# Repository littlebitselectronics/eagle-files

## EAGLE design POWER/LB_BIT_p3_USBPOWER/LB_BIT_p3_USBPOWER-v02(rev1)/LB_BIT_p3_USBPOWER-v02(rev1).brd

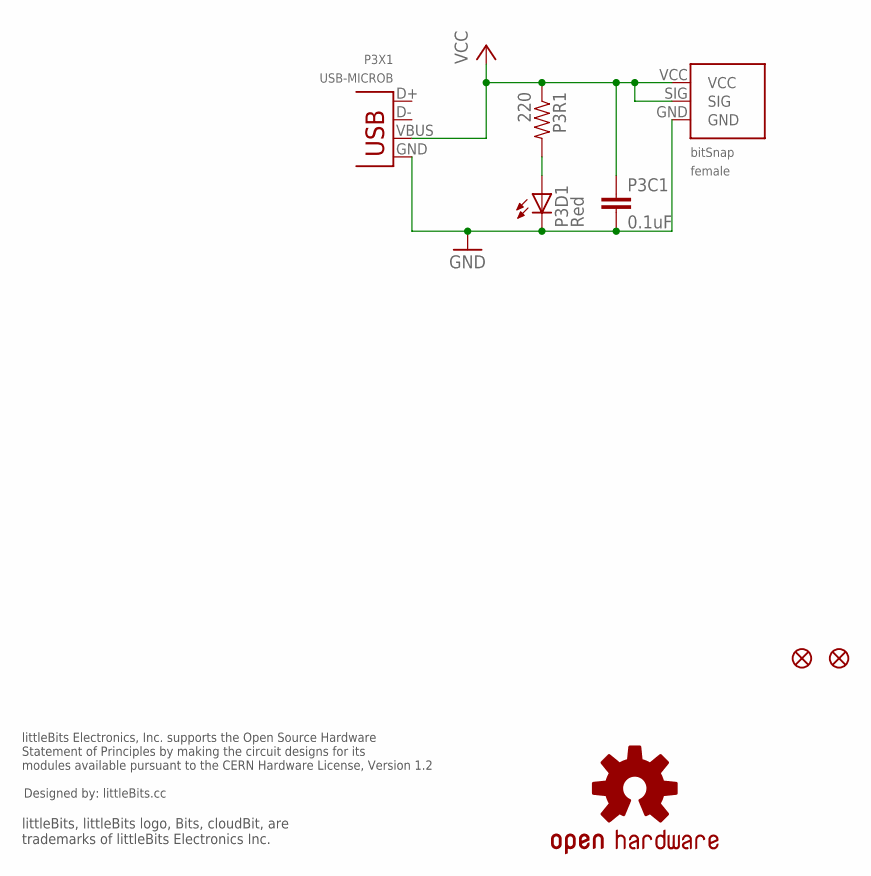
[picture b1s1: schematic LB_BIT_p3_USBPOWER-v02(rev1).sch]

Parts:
P3BSF: BITSNAP_FEMALE
P3C1: 0.1uF; 0603-CAP
P3D1: Red; LED-1206
P3FD1, P3FD2: FIDUCIAL1X2; FIDUCIAL-1X2
P3R1: 220; 0603-RES
P3X1: USB-MICROB; USB-MICROB-ZX62-B-5PA(11)
U$2: OSHWCREDIT
U$3: OSHW-LOGOL; OSHW-LOGO-L

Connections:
GND: P3BSF.GND, P3C1.2, P3D1.C, P3X1.GND
unnamed: P3D1.A, P3R1.2
VCC: P3BSF.SIG, P3BSF.VCC, P3C1.1, P3R1.1, P3X1.VBUS

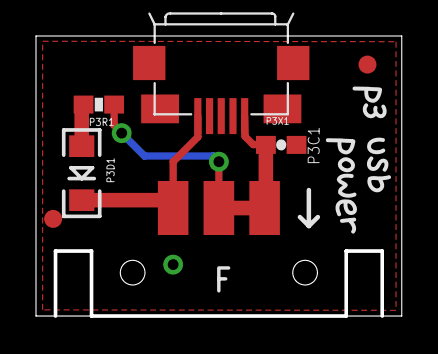
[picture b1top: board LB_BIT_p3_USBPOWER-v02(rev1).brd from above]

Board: 2 copper layers, 20.3 x 15.6 mm, 20 parts (0 on the bottom side), 3 nets.

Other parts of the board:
U$1, U$10: P
U$4: OSHW_FILLX150_NOTEXT
U$6: 3
U$7: U
U$8: S
U$9: B
U$11: O
U$12: W
U$13: E
U$14: R

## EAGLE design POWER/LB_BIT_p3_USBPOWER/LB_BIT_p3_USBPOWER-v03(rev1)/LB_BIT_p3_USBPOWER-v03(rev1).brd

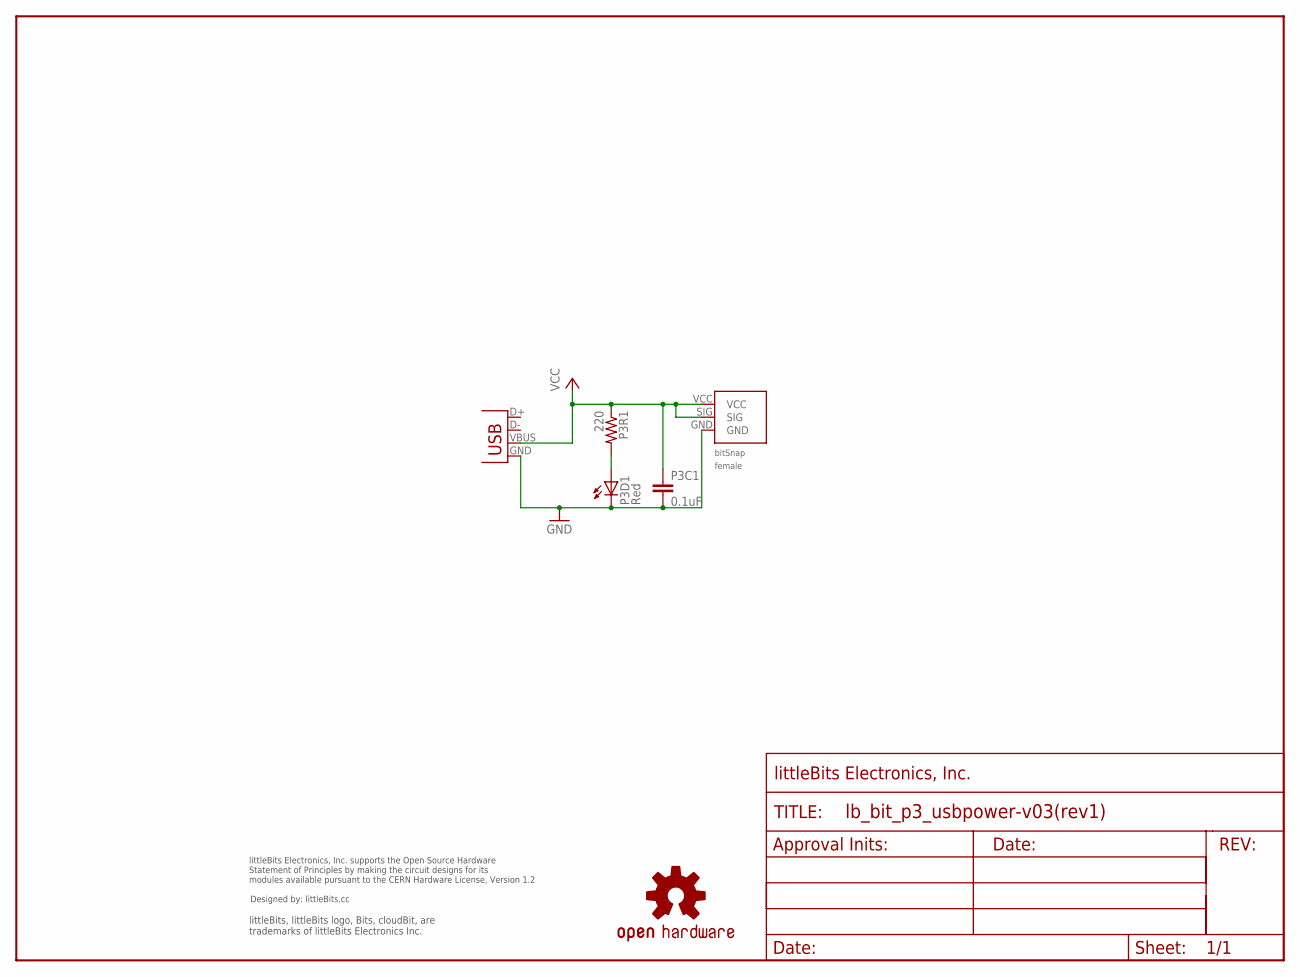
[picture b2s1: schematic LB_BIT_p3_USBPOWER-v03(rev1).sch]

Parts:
P3BSF1: BITSNAP_V03_FEMALE
P3C1: 0.1uF; 0603-CAP
P3D1: Red; LED-1206
P3R1: 220; 0603-RES
P3X1: USB-MICROB-AUK_TH; USB-MICROB-AUK
U$1: OSHWCREDIT
U$2: FRAME-LETTER-OHWOHW; FABDWG01-OHW
U$3: OSHW-LOGOL; OSHW-LOGO-L

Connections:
GND: P3BSF1.GND, P3C1.2, P3D1.C, P3X1.GND
unnamed: P3D1.A, P3R1.2
VCC: P3BSF1.SIG, P3BSF1.VCC, P3C1.1, P3R1.1, P3X1.VBUS

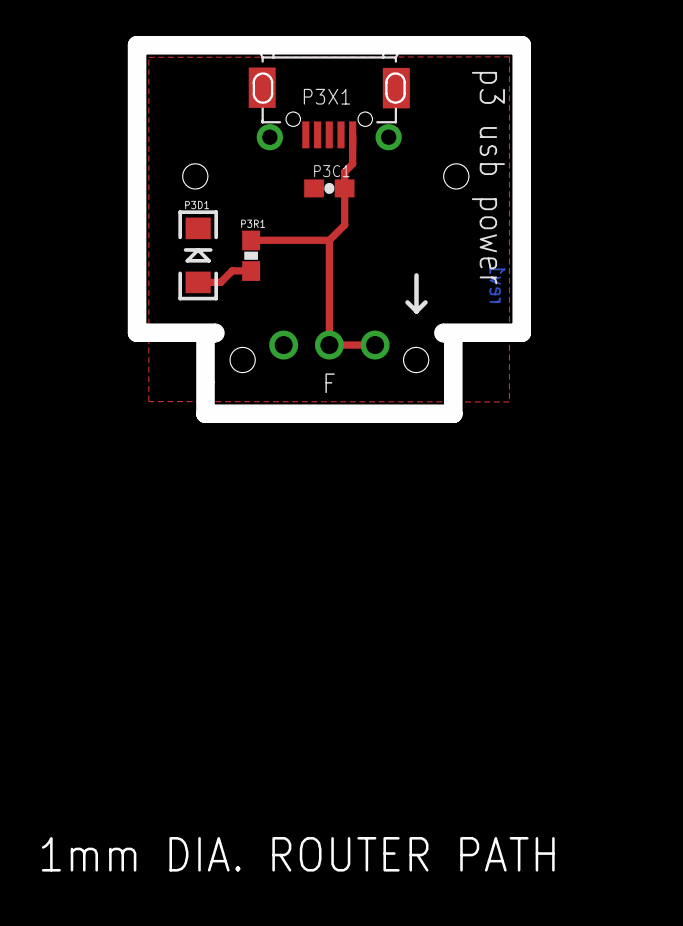
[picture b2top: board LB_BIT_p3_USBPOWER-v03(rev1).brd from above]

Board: 2 copper layers, 21.4 x 20.5 mm, 10 parts (0 on the bottom side), 3 nets.

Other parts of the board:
U$4: OSHW_FILLX150_NOTEXT
U$15: LB_PWR_LEGS

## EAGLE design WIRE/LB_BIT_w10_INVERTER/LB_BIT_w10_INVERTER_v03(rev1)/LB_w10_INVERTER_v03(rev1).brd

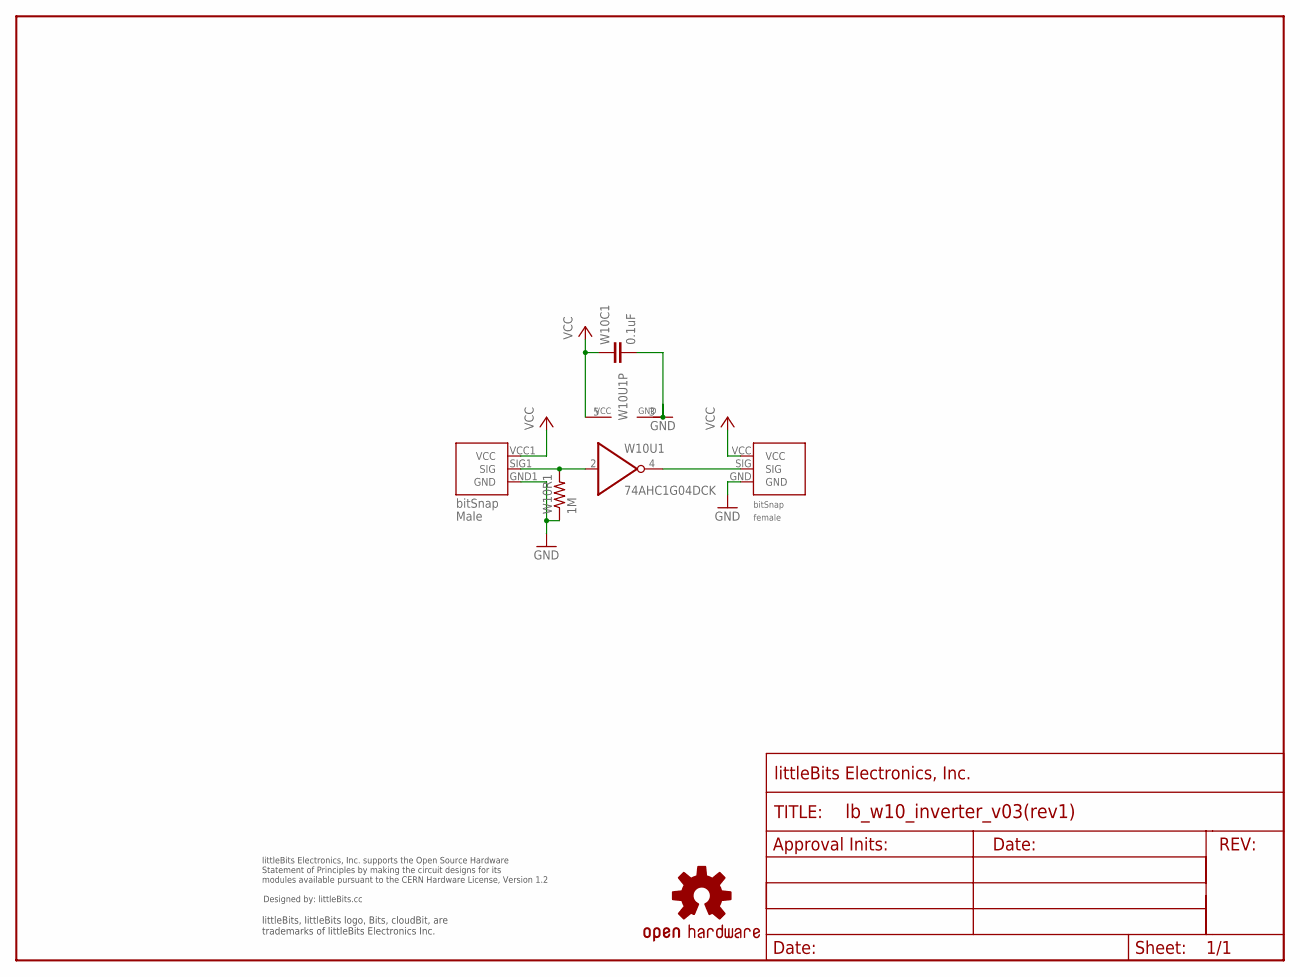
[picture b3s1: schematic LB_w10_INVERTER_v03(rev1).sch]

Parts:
U$1: FRAME-LETTER-OHWOHW; FABDWG01-OHW
U$3: OSHWCREDIT
U$4: OSHW-LOGOL; OSHW-LOGO-L
W10BSF1: BITSNAP_V03_FEMALE
W10BSM1: BITSNAP_V03_MALE
W10C1: 0.1uF; 0603-CAP
W10R1: 1M; 0603-RES
W10U1: 74AHC1G04DCK; SC70-5

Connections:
GND: W10BSF1.GND, W10BSM1.GND1 (GND), W10C1.2, W10R1.1, W10U1.3 (GND)
unnamed: W10BSM1.SIG1 (SIG), W10R1.2, W10U1.2 (I)
unnamed: W10BSF1.SIG, W10U1.4 (O)
VCC: W10BSF1.VCC, W10BSM1.VCC1 (VCC), W10C1.1, W10U1.5 (VCC)

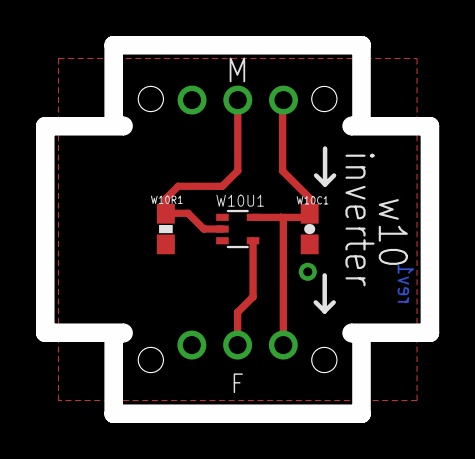
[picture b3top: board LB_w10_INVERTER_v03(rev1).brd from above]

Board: 2 copper layers, 21.4 x 20.5 mm, 9 parts (0 on the bottom side), 4 nets.

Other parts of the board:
U$2: OSHW_FILLX150_NOTEXT

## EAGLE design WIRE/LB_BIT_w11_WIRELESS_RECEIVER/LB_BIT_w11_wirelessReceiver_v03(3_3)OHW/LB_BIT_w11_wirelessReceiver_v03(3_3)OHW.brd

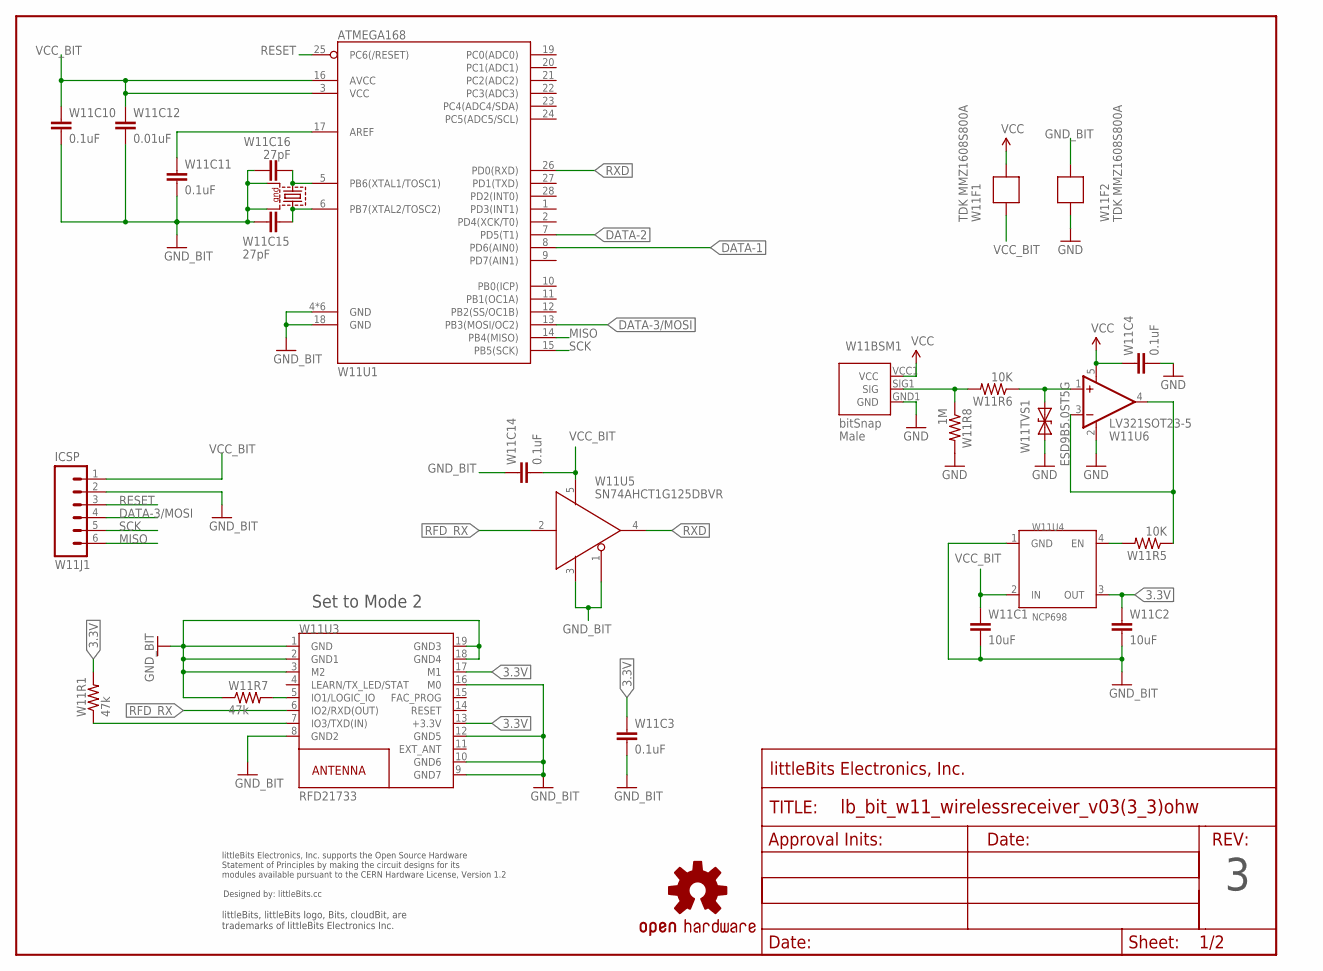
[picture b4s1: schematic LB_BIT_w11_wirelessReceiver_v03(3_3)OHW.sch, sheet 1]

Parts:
FRAME1: FRAME-LETTER-OHWOHW; FABDWG01-OHW
U$3: OSHW-LOGOL; OSHW-LOGO-L
U$7: OSHWCREDIT
W11BSM1: BITSNAP_V03_MALE
W11C1, W11C2: 10uF; CAP-0603
W11C3, W11C4, W11C10, W11C11, W11C14: 0.1uF; CAP-0603
W11C12: 0.01uF; CAP-0603
W11C15, W11C16: 27pF; CAP-0603
W11F1, W11F2: TDK MMZ1608S800A; R0603
W11J1: ICSP; SIP6-SM-0.1IN-NOS.S.
W11R1, W11R7: 47k; RES-0603
W11R5, W11R6: 10K; RES-0603
W11R8: 1M; RES-0603
W11TVS1: ESD9B5.0ST5G; SOD-923
W11U1: ATMEGA168; VQFN28
W11U3: RFD21733
W11U4: NCP698; NCP698_SC82-AB
W11U5: SN74AHCT1G125DBVR; SOT23-5
W11U6: LV321SOT23-5; SOT23-5
W11X1: 7B-8.000MAAJ-T; CRYSTAL-SMD-7B-SERIES-5X3.2MM

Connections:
3.3V: W11C2.1, W11C3.1, W11R1.2, W11U3.13 (+3.3V), W11U3.17 (M1), W11U4.3 (OUT)
DATA-1: W11U1.8 (PD6(AIN0)); also elsewhere on the board
DATA-2: W11U1.7 (PD5(T1)); also elsewhere on the board
DATA-3/MOSI: W11J1.4, W11U1.13 (PB3(MOSI/OC2)); also elsewhere on the board
ENABLE: W11R5.2, W11U4.4 (EN)
GND: W11BSM1.GND1 (GND), W11C4.2, W11F2.2, W11R8.2, W11TVS1.1 (A), W11U6.2 (V-); also elsewhere on the board
GND_BIT: W11C1.2, W11C2.2, W11C3.2, W11C10.2, W11C11.2, W11C12.2, W11C14.1, W11C15.2, W11C16.1, W11F2.1, W11J1.2, W11R7.1, W11U1.4 (GND), W11U1.18 (GND), W11U1.TH (GND), W11U1.TH@1 (GND), W11U1.TH@2 (GND), W11U1.TH@3 (GND), W11U1.TH@4 (GND), W11U3.1 (GND), W11U3.2 (GND1), W11U3.3 (M2), W11U3.8 (GND2), W11U3.9 (GND7), W11U3.10 (GND6), W11U3.12 (GND5), W11U3.16 (M0), W11U3.18 (GND4), W11U3.19 (GND3), W11U4.1 (GND), W11U5.1, W11U5.3, W11X1.P$2 (2), W11X1.P$4 (4)
MISO: W11J1.6, W11U1.14 (PB4(MISO))
unnamed: W11R6.1, W11TVS1.2 (C), W11U6.1 (+IN)
unnamed: W11C11.1, W11U1.17 (AREF)
unnamed: W11R7.2, W11U3.5 (IO1/LOGIC_IO)
unnamed: W11BSM1.SIG1 (SIG), W11R6.2, W11R8.1
unnamed: W11C16.2, W11U1.5 (PB6(XTAL1/TOSC1)), W11X1.P$1 (1)
unnamed: W11C15.1, W11U1.6 (PB7(XTAL2/TOSC2)), W11X1.P$3 (3)
unnamed: W11R5.1, W11U6.3 (-IN), W11U6.4 (OUT)
RESET: W11J1.3, W11U1.25 (PC6(/RESET))
RFD_RX: W11U3.6 (IO2/RXD(OUT)), W11U5.2
RFD_TX: W11R1.1, W11U3.7 (IO3/TXD(IN))
RXD: W11U1.26 (PD0(RXD)), W11U5.4
SCK: W11J1.5, W11U1.15 (PB5(SCK))
VCC: W11BSM1.VCC1 (VCC), W11C4.1, W11F1.1, W11U6.5 (V+); also elsewhere on the board
VCC_BIT: W11C1.1, W11C10.1, W11C12.1, W11C14.2, W11F1.2, W11J1.1, W11U1.3 (VCC), W11U1.16 (AVCC), W11U4.2 (IN), W11U5.5

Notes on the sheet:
Set to Mode 2

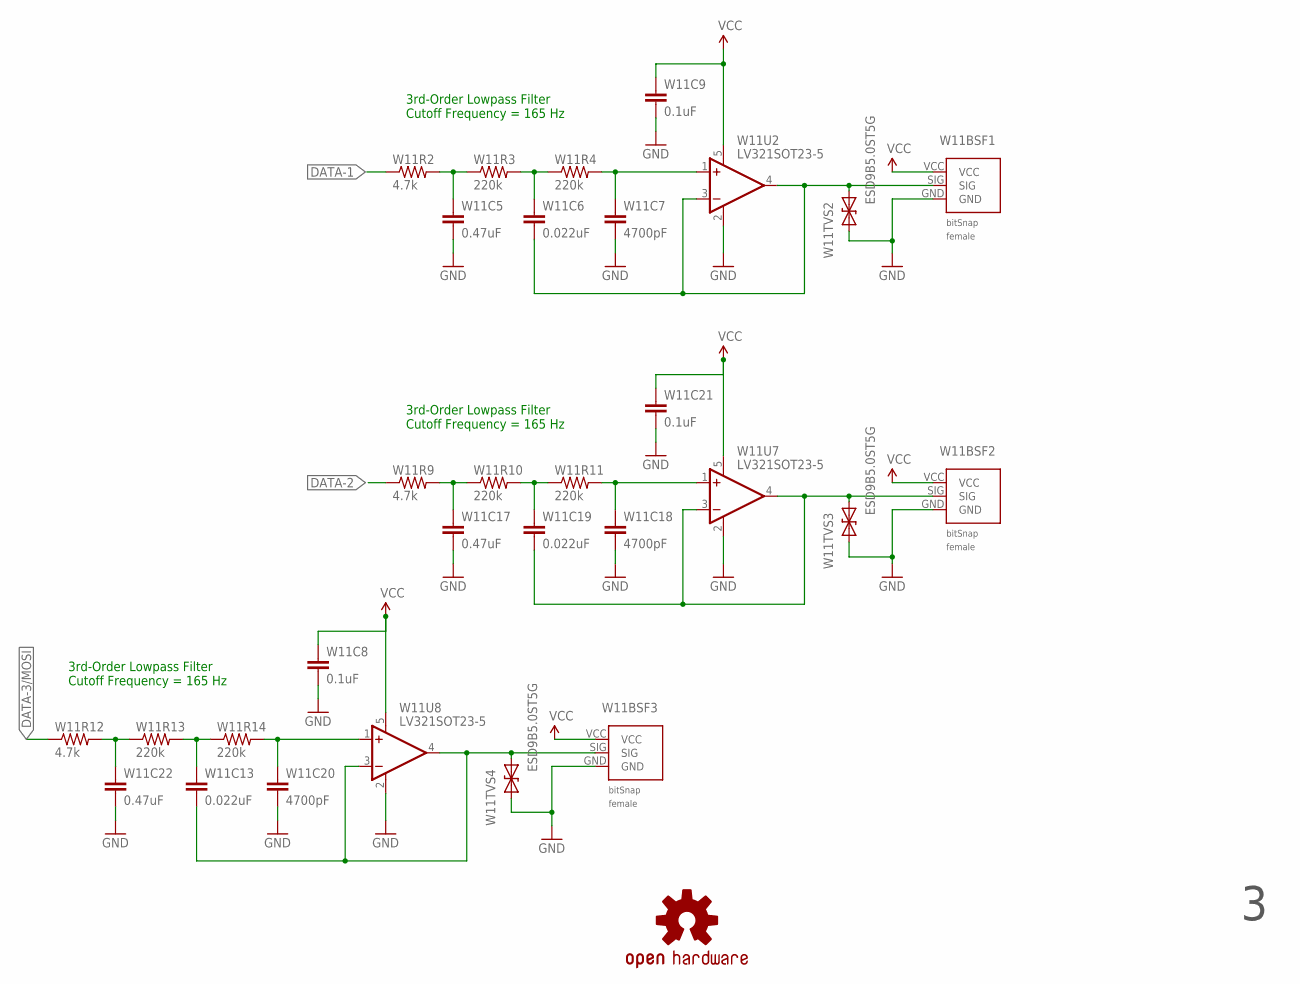
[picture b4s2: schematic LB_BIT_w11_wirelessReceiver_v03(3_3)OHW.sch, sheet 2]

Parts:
U$9: OSHW-LOGOL; OSHW-LOGO-L
W11BSF1, W11BSF2, W11BSF3: BITSNAP_V03_FEMALE
W11C5, W11C17, W11C22: 0.47uF; CAP-0603
W11C6, W11C13, W11C19: 0.022uF; CAP-0603
W11C7, W11C18, W11C20: 4700pF; CAP-0603
W11C8, W11C9, W11C21: 0.1uF; CAP-0603
W11R2, W11R9, W11R12: 4.7k; RES-0603
W11R3, W11R4, W11R10, W11R11, W11R13, W11R14: 220k; RES-0603
W11TVS2, W11TVS3, W11TVS4: ESD9B5.0ST5G; SOD-923
W11U2, W11U7, W11U8: LV321SOT23-5; SOT23-5

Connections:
DATA-1: W11R2.1; also elsewhere on the board
DATA-2: W11R9.1; also elsewhere on the board
DATA-3/MOSI: W11R12.1; also elsewhere on the board
GND: W11BSF1.GND, W11BSF2.GND, W11BSF3.GND, W11C5.2, W11C7.2, W11C8.2, W11C9.2, W11C17.2, W11C18.2, W11C20.2, W11C21.2, W11C22.2, W11TVS2.1 (A), W11TVS3.1 (A), W11TVS4.1 (A), W11U2.2 (V-), W11U7.2 (V-), W11U8.2 (V-); also elsewhere on the board
unnamed: W11C6.1, W11R3.2, W11R4.1
unnamed: W11C5.1, W11R2.2, W11R3.1
unnamed: W11C7.1, W11R4.2, W11U2.1 (+IN)
unnamed: W11C17.1, W11R9.2, W11R10.1
unnamed: W11C18.1, W11R11.2, W11U7.1 (+IN)
unnamed: W11C19.1, W11R10.2, W11R11.1
unnamed: W11C22.1, W11R12.2, W11R13.1
unnamed: W11C20.1, W11R14.2, W11U8.1 (+IN)
unnamed: W11C13.1, W11R13.2, W11R14.1
OUT-1: W11BSF1.SIG, W11C6.2, W11TVS2.2 (C), W11U2.3 (-IN), W11U2.4 (OUT)
OUT-2: W11BSF2.SIG, W11C19.2, W11TVS3.2 (C), W11U7.3 (-IN), W11U7.4 (OUT)
OUT-3: W11BSF3.SIG, W11C13.2, W11TVS4.2 (C), W11U8.3 (-IN), W11U8.4 (OUT)
VCC: W11BSF1.VCC, W11BSF2.VCC, W11BSF3.VCC, W11C8.1, W11C9.1, W11C21.1, W11U2.5 (V+), W11U7.5 (V+), W11U8.5 (V+); also elsewhere on the board

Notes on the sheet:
3rd-Order Lowpass Filter Cutoff Frequency = 165 Hz

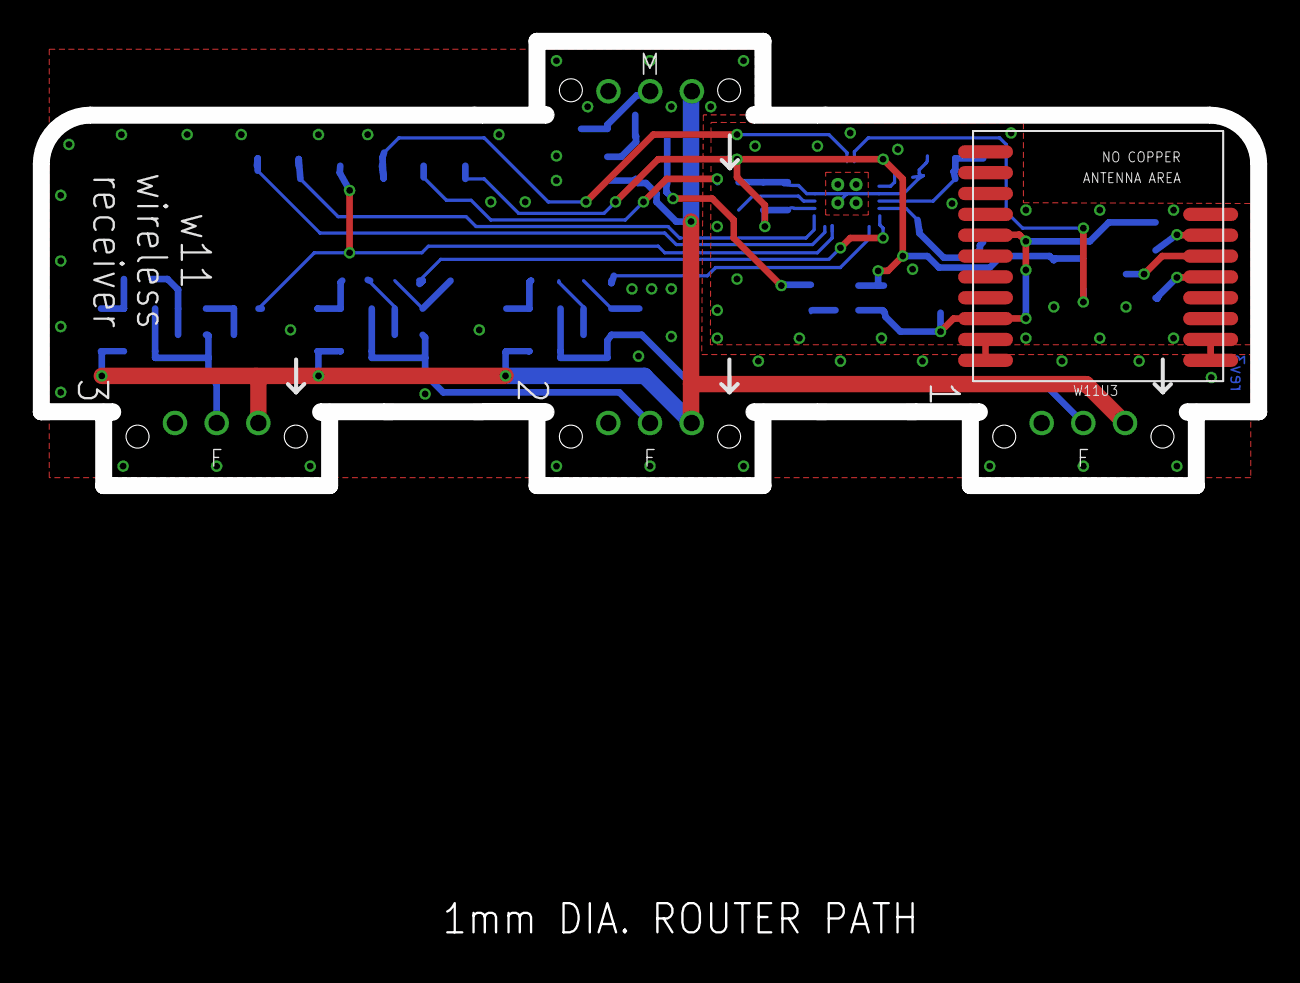
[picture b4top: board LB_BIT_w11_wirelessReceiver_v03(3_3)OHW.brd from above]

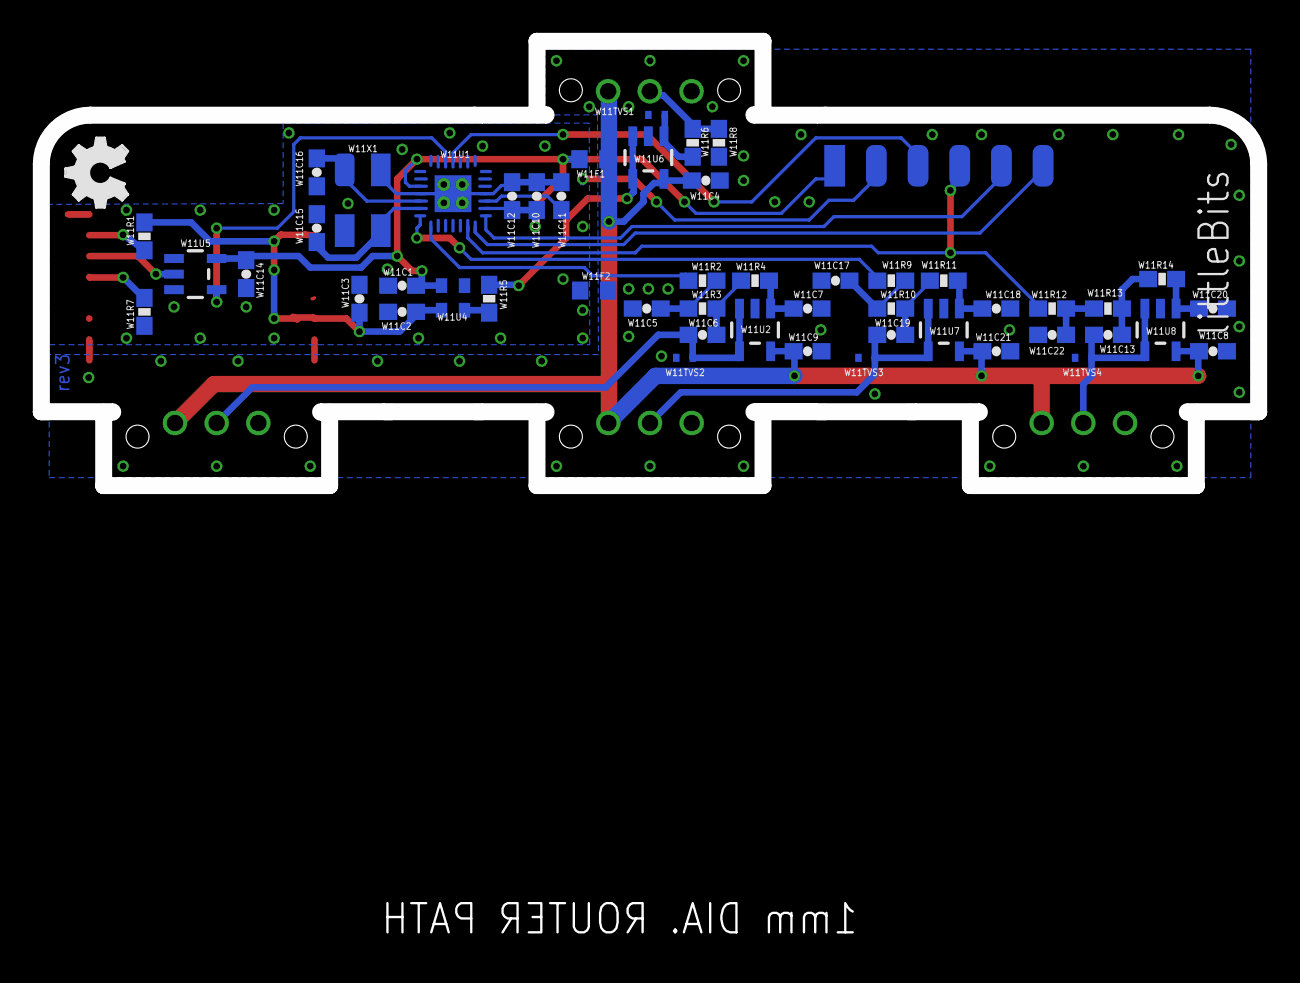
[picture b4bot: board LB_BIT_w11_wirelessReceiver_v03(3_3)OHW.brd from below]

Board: 2 copper layers, 74.2 x 27.1 mm, 61 parts (51 on the bottom side), 34 nets.

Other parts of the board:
U$21: OSHW_FILLX150_NOTEXT

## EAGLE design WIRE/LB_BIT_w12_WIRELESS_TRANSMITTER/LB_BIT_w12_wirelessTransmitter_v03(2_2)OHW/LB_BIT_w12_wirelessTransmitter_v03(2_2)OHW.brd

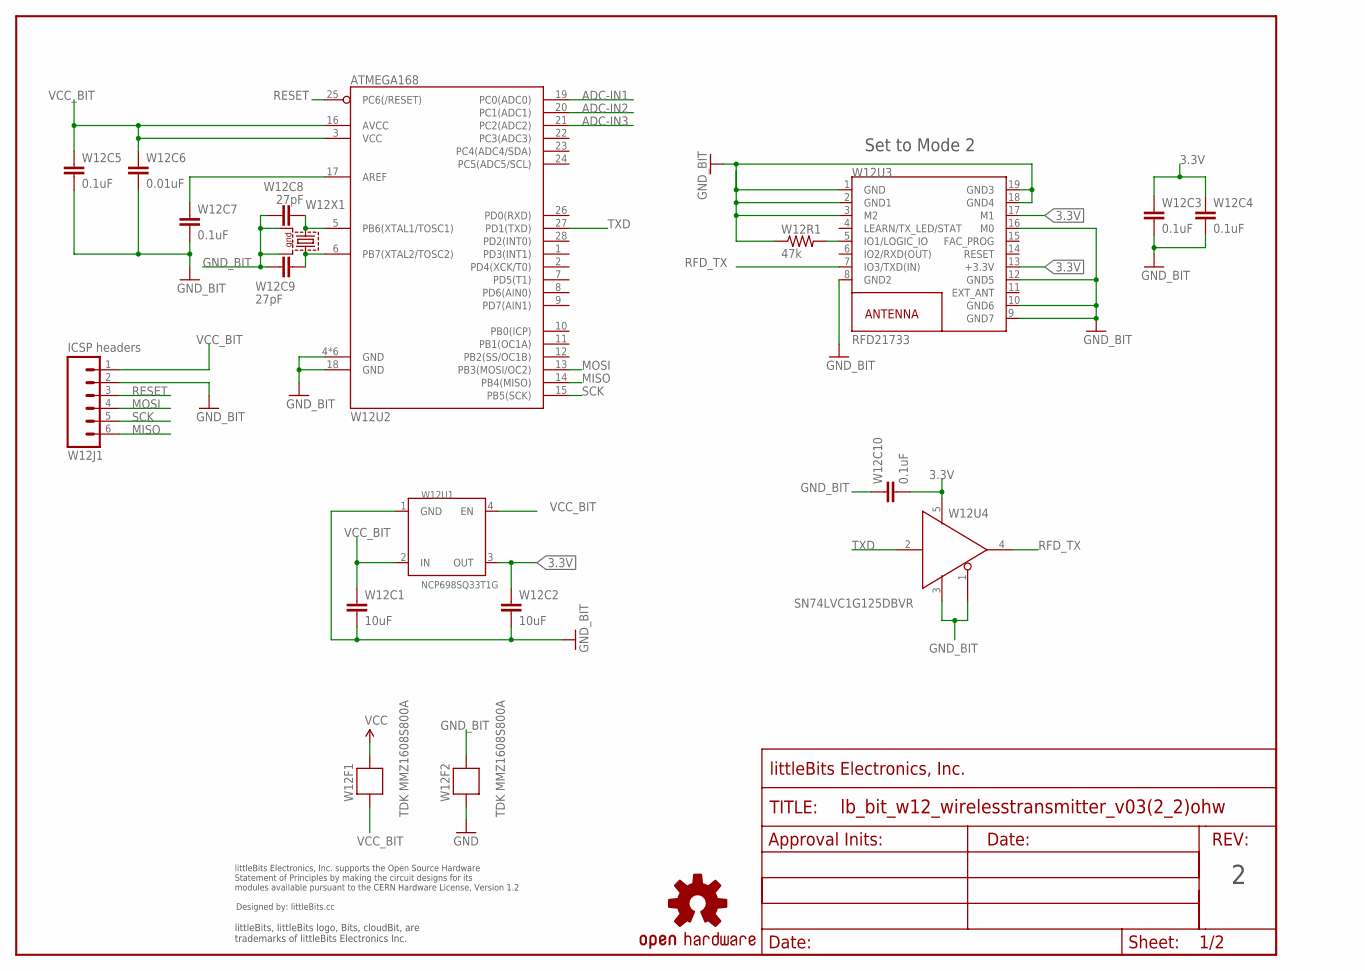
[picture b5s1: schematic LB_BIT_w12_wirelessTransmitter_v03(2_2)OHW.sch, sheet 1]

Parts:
FRAME1: FRAME-LETTER-OHWOHW; FABDWG01-OHW
U$15: OSHWCREDIT
U$31: OSHW-LOGOL; OSHW-LOGO-L
W12C1, W12C2: 10uF; CAP-0603
W12C3, W12C4, W12C5, W12C7, W12C10: 0.1uF; 0603-CAP
W12C6: 0.01uF; 0603-CAP
W12C8, W12C9: 27pF; CAP-0603
W12F1, W12F2: TDK MMZ1608S800A; R0603
W12J1: ICSP headers; SIP6-SM-0.1IN-NOS.S.
W12R1: 47k; 0603-RES
W12U1: NCP698SQ33T1G; NCP698_SC82-AB
W12U2: ATMEGA168; VQFN28
W12U3: RFD21733
W12U4: SN74LVC1G125DBVR; SOT23-5
W12X1: 8MHz; CRYSTAL-SMD-7B-SERIES-5X3.2MM

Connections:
3.3V: W12C2.1, W12C3.1, W12C4.1, W12C10.2, W12U1.3 (OUT), W12U3.13 (+3.3V), W12U3.17 (M1), W12U4.5
ADC-IN1: W12U2.19 (PC0(ADC0)); also elsewhere on the board
ADC-IN2: W12U2.20 (PC1(ADC1)); also elsewhere on the board
ADC-IN3: W12U2.21 (PC2(ADC2)); also elsewhere on the board
GND: W12F2.2; also elsewhere on the board
GND_BIT: W12C1.2, W12C2.2, W12C3.2, W12C4.2, W12C5.2, W12C6.2, W12C7.2, W12C8.1, W12C9.2, W12C10.1, W12F2.1, W12J1.2, W12R1.1, W12U1.1 (GND), W12U2.4 (GND), W12U2.18 (GND), W12U2.TH (GND), W12U2.TH@1 (GND), W12U2.TH@2 (GND), W12U2.TH@3 (GND), W12U2.TH@4 (GND), W12U3.1 (GND), W12U3.2 (GND1), W12U3.3 (M2), W12U3.8 (GND2), W12U3.9 (GND7), W12U3.10 (GND6), W12U3.12 (GND5), W12U3.16 (M0), W12U3.18 (GND4), W12U3.19 (GND3), W12U4.1, W12U4.3, W12X1.P$2 (2), W12X1.P$4 (4)
MISO: W12J1.6, W12U2.14 (PB4(MISO))
MOSI: W12J1.4, W12U2.13 (PB3(MOSI/OC2))
unnamed: W12C7.1, W12U2.17 (AREF)
unnamed: W12R1.2, W12U3.5 (IO1/LOGIC_IO)
unnamed: W12C8.2, W12U2.5 (PB6(XTAL1/TOSC1)), W12X1.P$1 (1)
unnamed: W12C9.1, W12U2.6 (PB7(XTAL2/TOSC2)), W12X1.P$3 (3)
RESET: W12J1.3, W12U2.25 (PC6(/RESET))
RFD_TX: W12U3.7 (IO3/TXD(IN)), W12U4.4
SCK: W12J1.5, W12U2.15 (PB5(SCK))
TXD: W12U2.27 (PD1(TXD)), W12U4.2
VCC: W12F1.1; also elsewhere on the board
VCC_BIT: W12C1.1, W12C5.1, W12C6.1, W12F1.2, W12J1.1, W12U1.2 (IN), W12U1.4 (EN), W12U2.3 (VCC), W12U2.16 (AVCC)

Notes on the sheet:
Set to Mode 2
W12X1

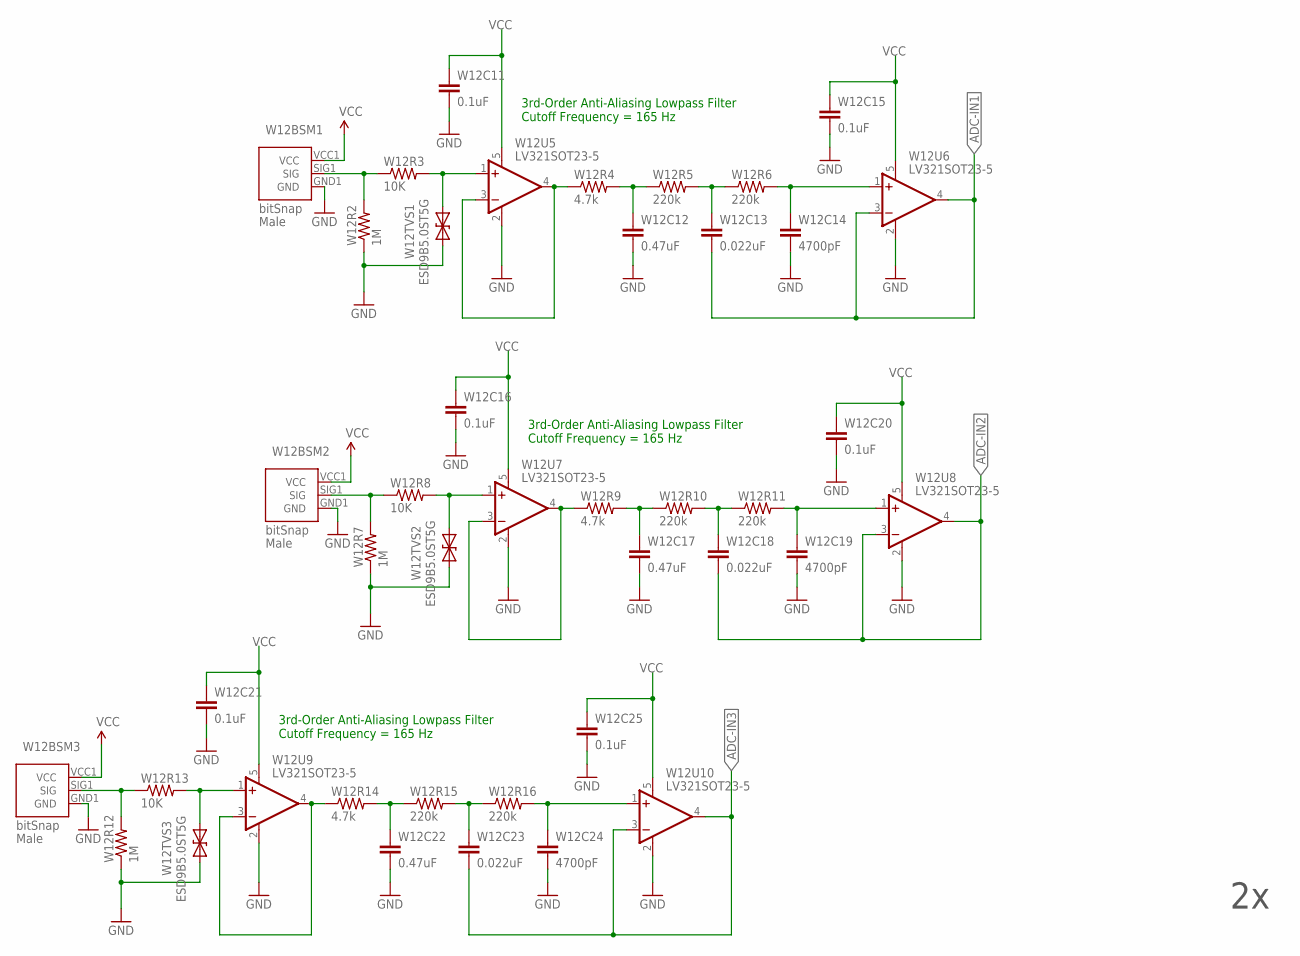
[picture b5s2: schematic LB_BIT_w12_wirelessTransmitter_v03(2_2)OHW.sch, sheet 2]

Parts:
W12BSM1, W12BSM2, W12BSM3: BITSNAP_V03_MALE
W12C11, W12C15, W12C16, W12C20, W12C21, W12C25: 0.1uF; 0603-CAP
W12C12, W12C17, W12C22: 0.47uF; CAP-0603
W12C13, W12C18, W12C23: 0.022uF; CAP-0603
W12C14, W12C19, W12C24: 4700pF; CAP-0603
W12R2, W12R7, W12R12: 1M; 0603-RES
W12R3, W12R8, W12R13: 10K; 0603-RES
W12R4, W12R9, W12R14: 4.7k; RES-0603
W12R5, W12R6, W12R10, W12R11, W12R15, W12R16: 220k; RES-0603
W12TVS1, W12TVS2, W12TVS3: ESD9B5.0ST5G; SOD-923
W12U5, W12U6, W12U7, W12U8, W12U9, W12U10: LV321SOT23-5; SOT23-5

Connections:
ADC-IN1: W12C13.2, W12U6.3 (-IN), W12U6.4 (OUT); also elsewhere on the board
ADC-IN2: W12C18.2, W12U8.3 (-IN), W12U8.4 (OUT); also elsewhere on the board
ADC-IN3: W12C23.2, W12U10.3 (-IN), W12U10.4 (OUT); also elsewhere on the board
GND: W12BSM1.GND1 (GND), W12BSM2.GND1 (GND), W12BSM3.GND1 (GND), W12C11.2, W12C12.2, W12C14.2, W12C15.2, W12C16.2, W12C17.2, W12C19.2, W12C20.2, W12C21.2, W12C22.2, W12C24.2, W12C25.2, W12R2.1, W12R7.1, W12R12.1, W12TVS1.1 (A), W12TVS2.1 (A), W12TVS3.1 (A), W12U5.2 (V-), W12U6.2 (V-), W12U7.2 (V-), W12U8.2 (V-), W12U9.2 (V-), W12U10.2 (V-); also elsewhere on the board
unnamed: W12R3.2, W12TVS1.2 (C), W12U5.1 (+IN)
unnamed: W12C12.1, W12R4.2, W12R5.1
unnamed: W12C14.1, W12R6.2, W12U6.1 (+IN)
unnamed: W12R4.1, W12U5.3 (-IN), W12U5.4 (OUT)
unnamed: W12C13.1, W12R5.2, W12R6.1
unnamed: W12R8.2, W12TVS2.2 (C), W12U7.1 (+IN)
unnamed: W12C17.1, W12R9.2, W12R10.1
unnamed: W12C19.1, W12R11.2, W12U8.1 (+IN)
unnamed: W12R9.1, W12U7.3 (-IN), W12U7.4 (OUT)
unnamed: W12C18.1, W12R10.2, W12R11.1
unnamed: W12R13.2, W12TVS3.2 (C), W12U9.1 (+IN)
unnamed: W12C22.1, W12R14.2, W12R15.1
unnamed: W12C24.1, W12R16.2, W12U10.1 (+IN)
unnamed: W12R14.1, W12U9.3 (-IN), W12U9.4 (OUT)
unnamed: W12C23.1, W12R15.2, W12R16.1
SIG3: W12BSM1.SIG1 (SIG), W12R2.2, W12R3.1
SIG4: W12BSM2.SIG1 (SIG), W12R7.2, W12R8.1
SIG5: W12BSM3.SIG1 (SIG), W12R12.2, W12R13.1
VCC: W12BSM1.VCC1 (VCC), W12BSM2.VCC1 (VCC), W12BSM3.VCC1 (VCC), W12C11.1, W12C15.1, W12C16.1, W12C20.1, W12C21.1, W12C25.1, W12U5.5 (V+), W12U6.5 (V+), W12U7.5 (V+), W12U8.5 (V+), W12U9.5 (V+), W12U10.5 (V+); also elsewhere on the board

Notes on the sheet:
3rd-Order Anti-Aliasing Lowpass Filter Cutoff Frequency = 165 Hz

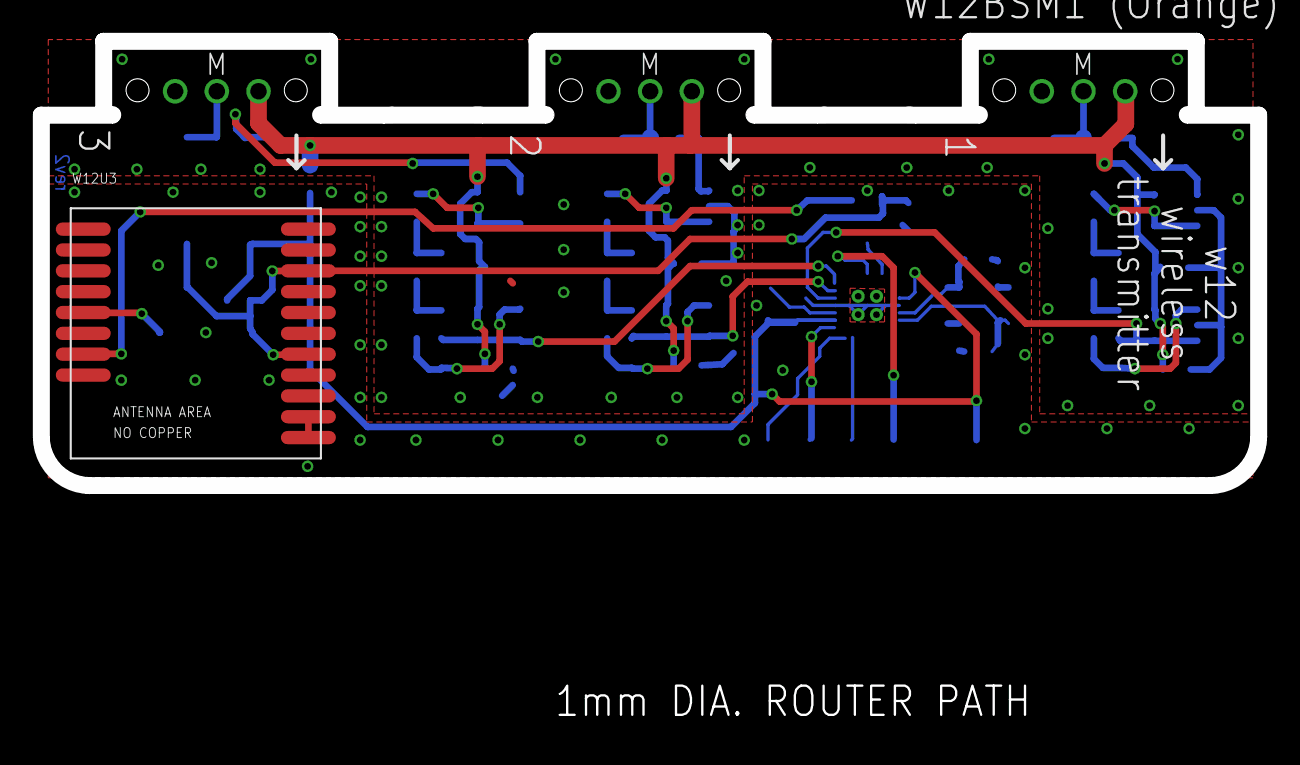
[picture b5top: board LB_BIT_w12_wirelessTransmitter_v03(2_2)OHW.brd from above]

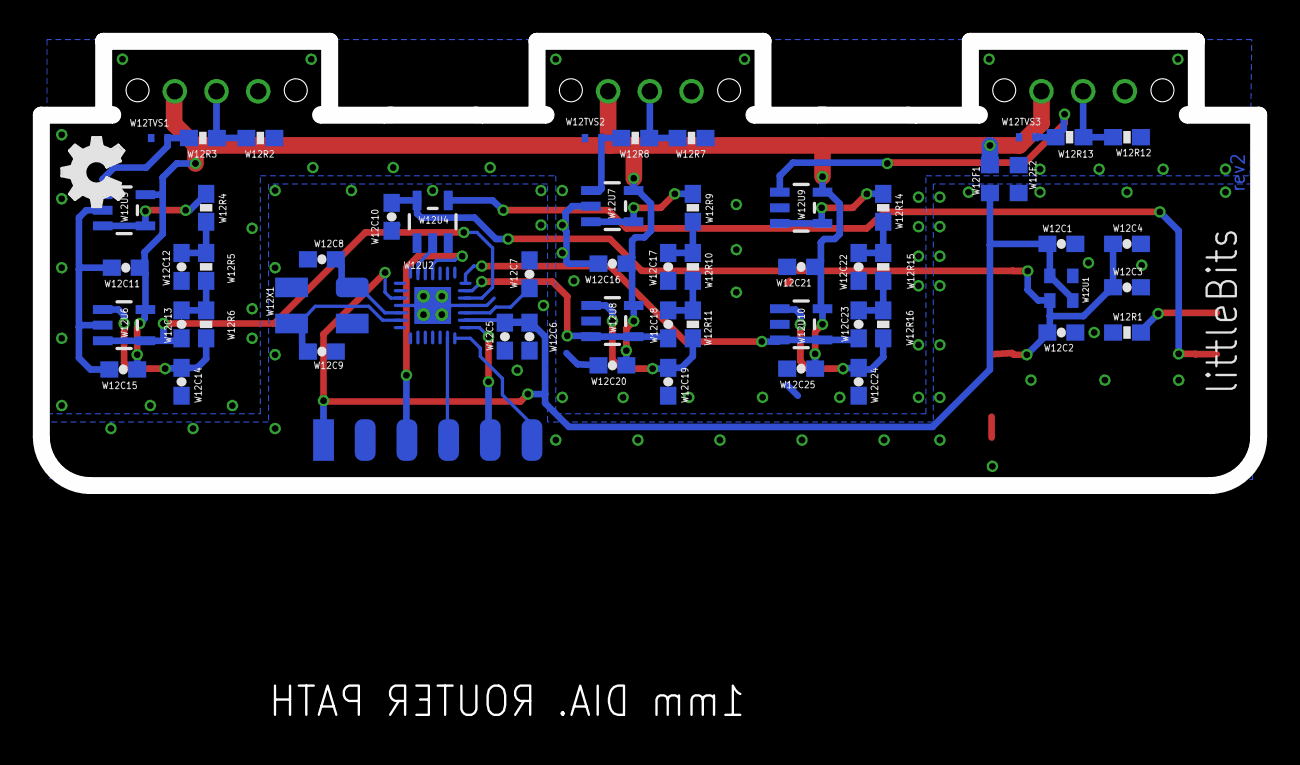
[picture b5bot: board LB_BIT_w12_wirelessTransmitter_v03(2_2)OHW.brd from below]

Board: 2 copper layers, 74.2 x 27.1 mm, 65 parts (57 on the bottom side), 36 nets.

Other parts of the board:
U$21: OSHW_FILLX150_NOTEXT

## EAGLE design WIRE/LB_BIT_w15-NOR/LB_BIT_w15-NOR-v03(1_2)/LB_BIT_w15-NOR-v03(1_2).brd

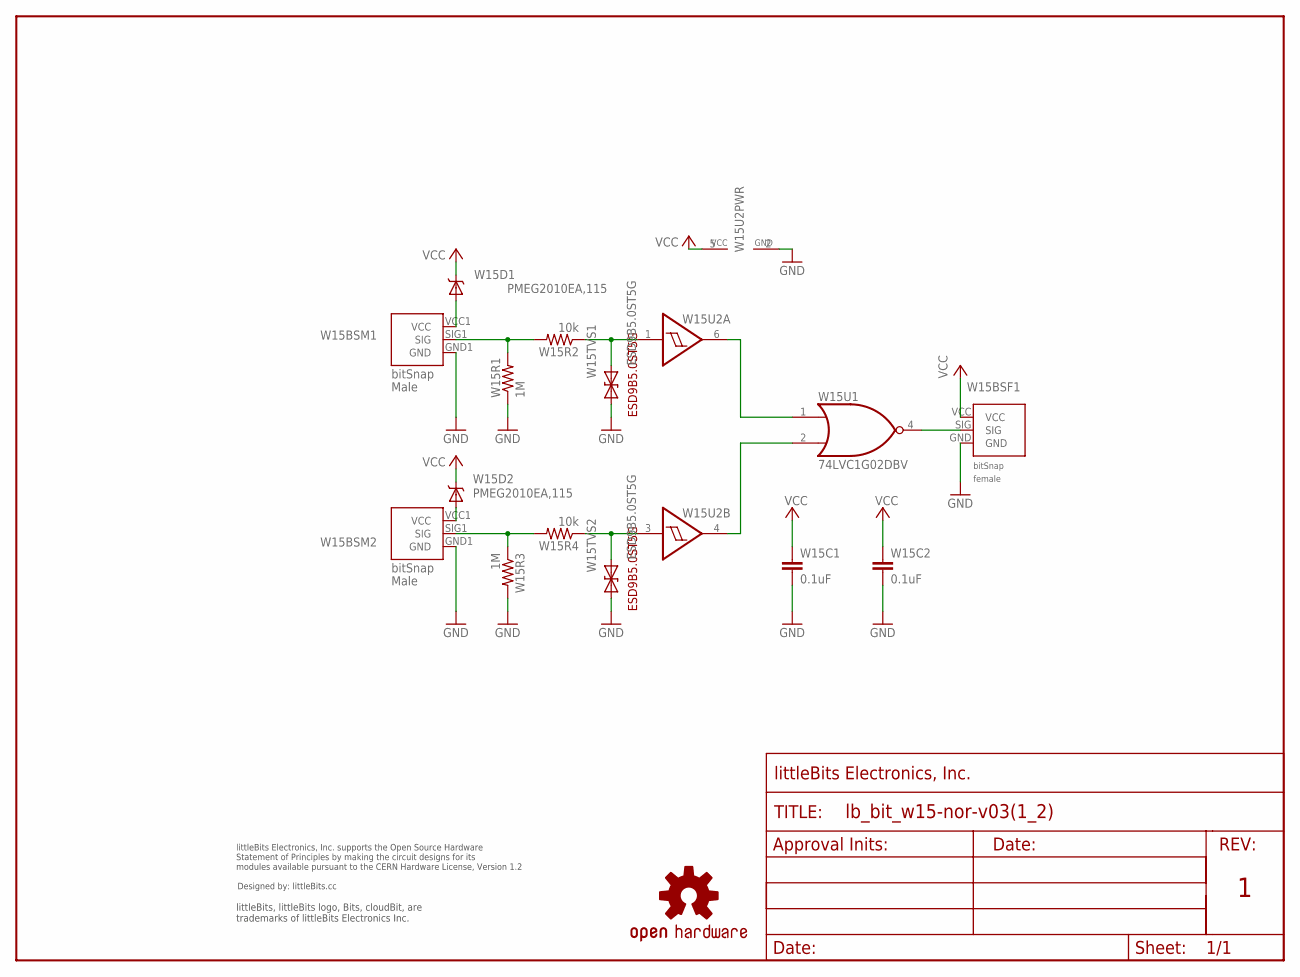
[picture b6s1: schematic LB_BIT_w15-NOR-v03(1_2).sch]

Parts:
U$1: OSHWCREDIT
U$2: OSHW-LOGOL; OSHW-LOGO-L
U$7: FRAME-LETTER-OHWOHW; FABDWG01-OHW
W15BSF1: BITSNAP_V03_FEMALE
W15BSM1, W15BSM2: BITSNAP_V03_MALE
W15C1, W15C2: 0.1uF; CAP-0603
W15D1, W15D2: PMEG2010EA,115; SOD-323
W15R1, W15R3: 1M; 0603-RES
W15R2, W15R4: 10k; 0603-RES
W15TVS1, W15TVS2: ESD9B5.0ST5G; SOD-923
W15U1: 74LVC1G02DBV; SOT23-5
W15U2: NC7WZ17; SC70-6

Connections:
GND: W15BSF1.GND, W15BSM1.GND1 (GND), W15BSM2.GND1 (GND), W15C1.2, W15C2.2, W15R1.1, W15R3.2, W15TVS1.1 (A), W15TVS2.1 (A), W15U1.3 (GND), W15U2.2 (GND)
unnamed: W15BSM2.SIG1 (SIG), W15R3.1, W15R4.2
unnamed: W15U1.1 (I0), W15U2.6 (O)
unnamed: W15BSM1.VCC1 (VCC), W15D1.2 (A)
unnamed: W15U1.2 (I1), W15U2.4 (O)
unnamed: W15BSM2.VCC1 (VCC), W15D2.2 (A)
unnamed: W15BSM1.SIG1 (SIG), W15R1.2, W15R2.2
unnamed: W15R2.1, W15TVS1.2 (C), W15U2.1 (I)
unnamed: W15R4.1, W15TVS2.2 (C), W15U2.3 (I)
unnamed: W15BSF1.SIG, W15U1.4 (O)
VCC: W15BSF1.VCC, W15C1.1, W15C2.1, W15D1.1 (C), W15D2.1 (C), W15U1.5 (VCC), W15U2.5 (VCC)

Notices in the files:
parts and their libraries:
LITTLEBITS: modules available pursuant to the CERN Hardware License,
Version 1.2
SparkFun_NEW: Licensing: CC v3.0 Share-Alike You are welcome to use this library for commercial purposes.
LITTLEBITS: modules available pursuant to the CERN Hardware License, Version 1.2
